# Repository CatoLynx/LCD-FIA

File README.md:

# What's this?
It's my project of converting an old LCD platform passenger information display to be fully customizable!

# BOMs
The BOM for the FIAControl main controller board can be found [here](https://catolynx.github.io/LCD-FIA/Hardware/FIAControl/bom/ibom.html).

The BOM for the FIAPi Raspberry Pi HAT adapter board can be found [here](https://catolynx.github.io/LCD-FIA/Hardware/FIAPi/bom/ibom.html).

# Pictures

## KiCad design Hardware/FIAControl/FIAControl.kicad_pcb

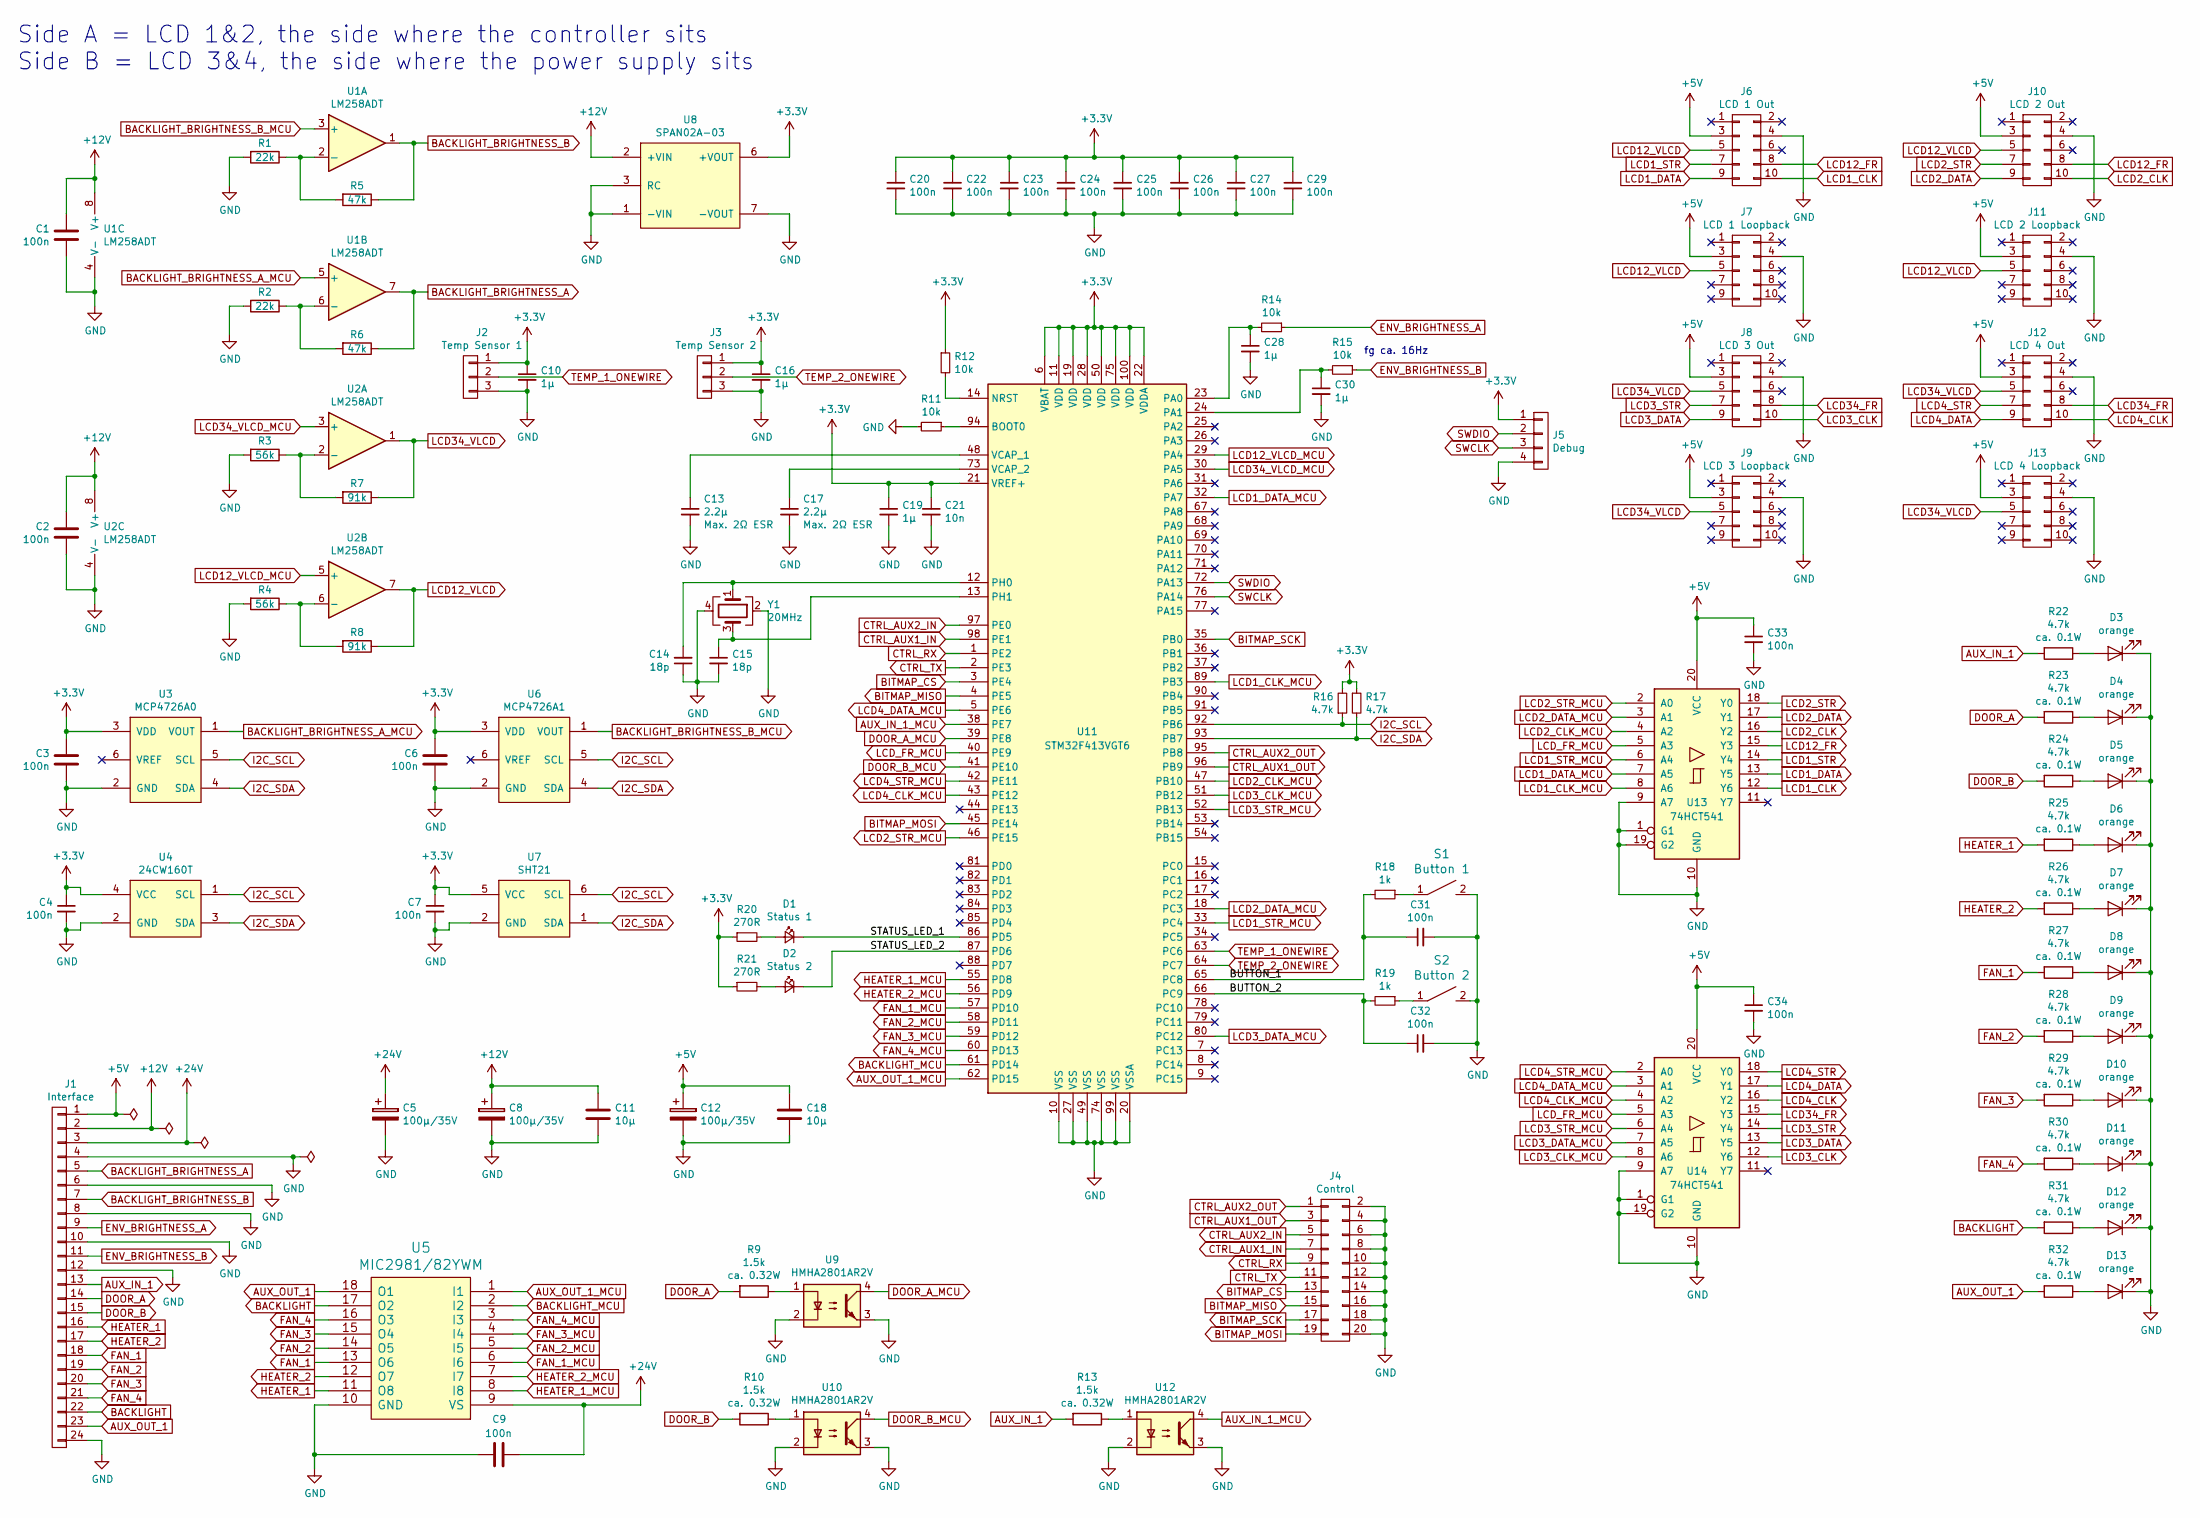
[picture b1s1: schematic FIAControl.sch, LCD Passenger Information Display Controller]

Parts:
C1, C2, C3, C4, C6, C7, C9, C31, C32, C33, C34: 100n; C_0603
C5, C8, C12: 100µ/35V; CP_Elec_6.3x7.7
C10, C16, C28, C30: 1µ; C_0805
C11, C18: 10µ; C_0805
C13, C17: 2.2µ; C_0402
C14, C15: 18p; C_0402
C19: 1µ; C_0402
C20, C22, C23, C24, C25, C26, C27, C29: 100n; C_0402
C21: 10n; C_0402
D1: Status 1; LED_0603
D2: Status 2; LED_0603
D3, D4, D5, D6, D7, D8, D9, D10, D11, D12, D13: orange; LED_0603
J1: Interface; Connector_DEGSON_DG246-3.81_24pin
J2: Temp Sensor 1; Molex_1718560003
J3: Temp Sensor 2; Molex_1718560003
J4: Control; IDC_Header_Straight_20pins
J5: Debug; Pin_Header_Straight_1x04
J6: LCD 1 Out; Connector_IDC_2mm_10pin_THT_Straight
J7: LCD 1 Loopback; Connector_IDC_2mm_10pin_THT_Straight
J8: LCD 3 Out; Connector_IDC_2mm_10pin_THT_Straight
J9: LCD 3 Loopback; Connector_IDC_2mm_10pin_THT_Straight
J10: LCD 2 Out; Connector_IDC_2mm_10pin_THT_Straight
J11: LCD 2 Loopback; Connector_IDC_2mm_10pin_THT_Straight
J12: LCD 4 Out; Connector_IDC_2mm_10pin_THT_Straight
J13: LCD 4 Loopback; Connector_IDC_2mm_10pin_THT_Straight
R1, R2: 22k; R_0603
R3, R4: 56k; R_0603
R5, R6: 47k; R_0603
R7, R8: 91k; R_0603
R9, R10, R13: 1.5k; R_1206
R11, R12, R14, R15: 10k; R_0603
R16, R17: 4.7k; R_0603
R18, R19: 1k; R_0603
R20, R21: 270R; R_0603
R22, R23, R24, R25, R26, R27, R28, R29, R30, R31, R32: 4.7k; R_0805
S1: Button 1; SW_SPST_SKQG
S2: Button 2; SW_SPST_SKQG
U1, U2: LM258ADT; SOIC-8_3.9x4.9mm_Pitch1.27mm
U3: MCP4726A0; SOT-23-6
U4: 24CW160T; SOT-23-5
U5: MIC2981/82YWM; SOIC-18W_7.5x11.6mm_Pitch1.27mm
U6: MCP4726A1; SOT-23-6
U7: SHT21; DFN6_3mmx3mm_EP_P1mm
U8: SPAN02A-03; DC_DC_Converter_MeanWell_SPAN
U9, U10, U12: HMHA2801AR2V; Optocoupler_MiniFlat_HalfPitch_4pin_SMD
U11: STM32F413VGT6; LQFP-100_14x14mm_Pitch0.5mm
U13, U14: 74HCT541; SOIC-20W_7.5x12.8mm_Pitch1.27mm
Y1: 20MHz; Crystal_SMD_2520-4pin_2.5x2.0mm

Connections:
+3V3: C3.2, C4.1, C6.2, C7.1, C10.1, C16.1, C19.1, C20.1, C21.1, C22.1, C23.1, C24.1, C25.1, C26.1, C27.1, C29.1, J2.1, J3.1, J5.1, R12.1, R16.2, R17.1, R20.1, R21.1, U3.3 (VDD), U4.4 (VCC), U6.3 (VDD), U7.5 (VCC), U8.6 (+VOUT), U11.6 (VBAT), U11.11 (VDD), U11.19 (VDD), U11.21 (VREF+), U11.22 (VDDA), U11.28 (VDD), U11.50 (VDD), U11.75 (VDD), U11.100 (VDD)
+5V: C12.1, C18.1, C33.1, C34.1, J1.1, J6.3, J7.3, J8.3, J9.3, J10.3, J11.3, J12.3, J13.3, U13.20 (VCC), U14.20 (VCC)
+12V: C1.2, C2.2, C8.1, C11.1, J1.2, U1.8 (V+), U2.8 (V+), U8.2 (+VIN)
+24V: C5.1, C9.2, J1.3, U5.9 (VS)
/BUTTON_1: C31.1, R18.2, U11.65 (PC8)
/BUTTON_2: C32.1, R19.2, U11.66 (PC9)
/STATUS_LED_1: D1.1 (K), U11.86 (PD5)
/STATUS_LED_2: D2.1 (K), U11.87 (PD6)
AUX_IN_1: J1.13, R13.2, R22.2
AUX_IN_1_MCU: U11.38 (PE7), U12.4
AUX_OUT_1: J1.23, R32.2, U5.18 (O1)
AUX_OUT_1_MCU: U5.1 (I1), U11.62 (PD15)
BACKLIGHT: J1.22, R31.2, U5.17 (O2)
BACKLIGHT_BRIGHTNESS_A: J1.5, R6.1, U1.7
BACKLIGHT_BRIGHTNESS_A_MCU: U1.5 (+), U3.1 (VOUT)
BACKLIGHT_BRIGHTNESS_B: J1.7, R5.1, U1.1
BACKLIGHT_BRIGHTNESS_B_MCU: U1.3 (+), U6.1 (VOUT)
BACKLIGHT_MCU: U5.2 (I2), U11.61 (PD14)
BITMAP_CS: J4.13, U11.3 (PE4)
BITMAP_MISO: J4.15, U11.4 (PE5)
BITMAP_MOSI: J4.19, U11.45 (PE14)
BITMAP_SCK: J4.17, U11.35 (PB0)
CTRL_AUX1_IN: J4.7, U11.98 (PE1)
CTRL_AUX1_OUT: J4.3, U11.96 (PB9)
CTRL_AUX2_IN: J4.5, U11.97 (PE0)
CTRL_AUX2_OUT: J4.1, U11.95 (PB8)
CTRL_RX: J4.9, U11.1 (PE2)
CTRL_TX: J4.11, U11.2 (PE3)
DOOR_A: J1.14, R9.2, R23.2
DOOR_A_MCU: U9.4, U11.39 (PE8)
DOOR_B: J1.15, R10.2, R24.2
DOOR_B_MCU: U10.4, U11.41 (PE10)
ENV_BRIGHTNESS_A: J1.9, R14.1
ENV_BRIGHTNESS_B: J1.11, R15.1
FAN_1: J1.18, R27.2, U5.13 (O6)
FAN_1_MCU: U5.6 (I6), U11.57 (PD10)
FAN_2: J1.19, R28.2, U5.14 (O5)
FAN_2_MCU: U5.5 (I5), U11.58 (PD11)
FAN_3: J1.20, R29.2, U5.15 (O4)
FAN_3_MCU: U5.4 (I4), U11.59 (PD12)
FAN_4: J1.21, R30.2, U5.16 (O3)
FAN_4_MCU: U5.3 (I3), U11.60 (PD13)
GND: C1.1, C2.1, C3.1, C4.2, C5.2, C6.1, C7.2, C8.2, C9.1, C10.2, C11.2, C12.2, C13.2, C14.1, C15.2, C16.2, C17.2, C18.2, C19.2, C20.2, C21.2, C22.2, C23.2, C24.2, C25.2, C26.2, C27.2, C28.2, C29.2, C30.2, C31.2, C32.2, C33.2, C34.2, D3.1 (K), D4.1 (K), D5.1 (K), D6.1 (K), D7.1 (K), D8.1 (K), D9.1 (K), D10.1 (K), D11.1 (K), D12.1 (K), D13.1 (K), J1.4, J1.6, J1.8, J1.10, J1.12, J1.24, J2.3, J3.3, J4.2, J4.4, J4.6, J4.8, J4.10, J4.12, J4.14, J4.16, J4.18, J4.20, J5.4, J6.4, J7.4, J8.4, J9.4, J10.4, J11.4, J12.4, J13.4, R1.2, R2.2, R3.2, R4.2, R11.2, S1.2, S2.2, U1.4 (V-), U2.4 (V-), U3.2 (GND), U4.2 (GND), U5.10 (GND), U6.2 (GND), U7.2 (GND), U8.1 (-VIN), U8.3 (RC), U8.7 (-VOUT), U9.2, U9.3, U10.2, U10.3, U11.10 (VSS), U11.20 (VSSA), U11.27 (VSS), U11.49 (VSS), U11.74 (VSS), U11.99 (VSS), U12.2, U12.3, U13.1 (G1), U13.9 (A7), U13.10 (GND), U13.19 (G2), U14.1 (G1), U14.9 (A7), U14.10 (GND), U14.19 (G2), Y1.2, Y1.4
HEATER_1: J1.16, R25.2, U5.11 (O8)
HEATER_1_MCU: U5.8 (I8), U11.55 (PD8)
HEATER_2: J1.17, R26.2, U5.12 (O7)
HEATER_2_MCU: U5.7 (I7), U11.56 (PD9)
I2C_SCL: R16.1, U3.5 (SCL), U4.1 (SCL), U6.5 (SCL), U7.6 (SCL), U11.92 (PB6)
I2C_SDA: R17.2, U3.4 (SDA), U4.3 (SDA), U6.4 (SDA), U7.1 (SDA), U11.93 (PB7)
LCD1_CLK: J6.10, U13.12 (Y6)
LCD1_CLK_MCU: U11.89 (PB3), U13.8 (A6)
LCD1_DATA: J6.9, U13.13 (Y5)
LCD1_DATA_MCU: U11.32 (PA7), U13.7 (A5)
LCD1_STR: J6.7, U13.14 (Y4)
LCD1_STR_MCU: U11.33 (PC4), U13.6 (A4)
LCD2_CLK: J10.10, U13.16 (Y2)
LCD2_CLK_MCU: U11.47 (PB10), U13.4 (A2)
LCD2_DATA: J10.9, U13.17 (Y1)
LCD2_DATA_MCU: U11.18 (PC3), U13.3 (A1)
LCD2_STR: J10.7, U13.18 (Y0)
LCD2_STR_MCU: U11.46 (PE15), U13.2 (A0)
LCD3_CLK: J8.10, U14.12 (Y6)
LCD3_CLK_MCU: U11.51 (PB12), U14.8 (A6)
LCD3_DATA: J8.9, U14.13 (Y5)
LCD3_DATA_MCU: U11.80 (PC12), U14.7 (A5)
LCD3_STR: J8.7, U14.14 (Y4)
LCD3_STR_MCU: U11.52 (PB13), U14.6 (A4)
LCD4_CLK: J12.10, U14.16 (Y2)
LCD4_CLK_MCU: U11.43 (PE12), U14.4 (A2)
LCD4_DATA: J12.9, U14.17 (Y1)
LCD4_DATA_MCU: U11.5 (PE6), U14.3 (A1)
LCD4_STR: J12.7, U14.18 (Y0)
LCD4_STR_MCU: U11.42 (PE11), U14.2 (A0)
LCD12_FR: J6.8, J10.8, U13.15 (Y3)
LCD12_VLCD: J6.5, J7.5, J10.5, J11.5, R8.1, U2.7
LCD12_VLCD_MCU: U2.5 (+), U11.29 (PA4)
LCD34_FR: J8.8, J12.8, U14.15 (Y3)
LCD34_VLCD: J8.5, J9.5, J12.5, J13.5, R7.1, U2.1
LCD34_VLCD_MCU: U2.3 (+), U11.30 (PA5)
LCD_FR_MCU: U11.40 (PE9), U13.5 (A3), U14.5 (A3)
unnamed: C13.1, U11.48 (VCAP_1)
unnamed: C14.2, U11.12 (PH0), Y1.1
unnamed: C15.1, U11.13 (PH1), Y1.3
unnamed: C17.1, U11.73 (VCAP_2)
unnamed: C28.1, R14.2, U11.23 (PA0)
unnamed: C30.1, R15.2, U11.24 (PA1)
unnamed: D1.2 (A), R20.2
unnamed: D2.2 (A), R21.2
unnamed: D3.2 (A), R22.1
unnamed: D4.2 (A), R23.1
unnamed: D5.2 (A), R24.1
unnamed: D6.2 (A), R25.1
unnamed: D7.2 (A), R26.1
unnamed: D8.2 (A), R27.1
unnamed: D9.2 (A), R28.1
unnamed: D10.2 (A), R29.1
unnamed: D11.2 (A), R30.1
unnamed: D12.2 (A), R31.1
unnamed: D13.2 (A), R32.1
unnamed: R1.1, R5.2, U1.2 (-)
unnamed: R2.1, R6.2, U1.6 (-)
unnamed: R3.1, R7.2, U2.2 (-)
unnamed: R4.1, R8.2, U2.6 (-)
unnamed: R9.1, U9.1
unnamed: R10.1, U10.1
unnamed: R11.1, U11.94 (BOOT0)
unnamed: R12.2, U11.14 (NRST)
unnamed: R13.1, U12.1
unnamed: R18.1, S1.1
unnamed: R19.1, S2.1
SWCLK: J5.3, U11.76 (PA14)
SWDIO: J5.2, U11.72 (PA13)
TEMP_1_ONEWIRE: J2.2, U11.63 (PC6)
TEMP_2_ONEWIRE: J3.2, U11.64 (PC7)

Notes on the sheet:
Side A = LCD 1&2, the side where the controller sits Side B = LCD 3&4, the side where the power supply sits
fg ca. 16Hz

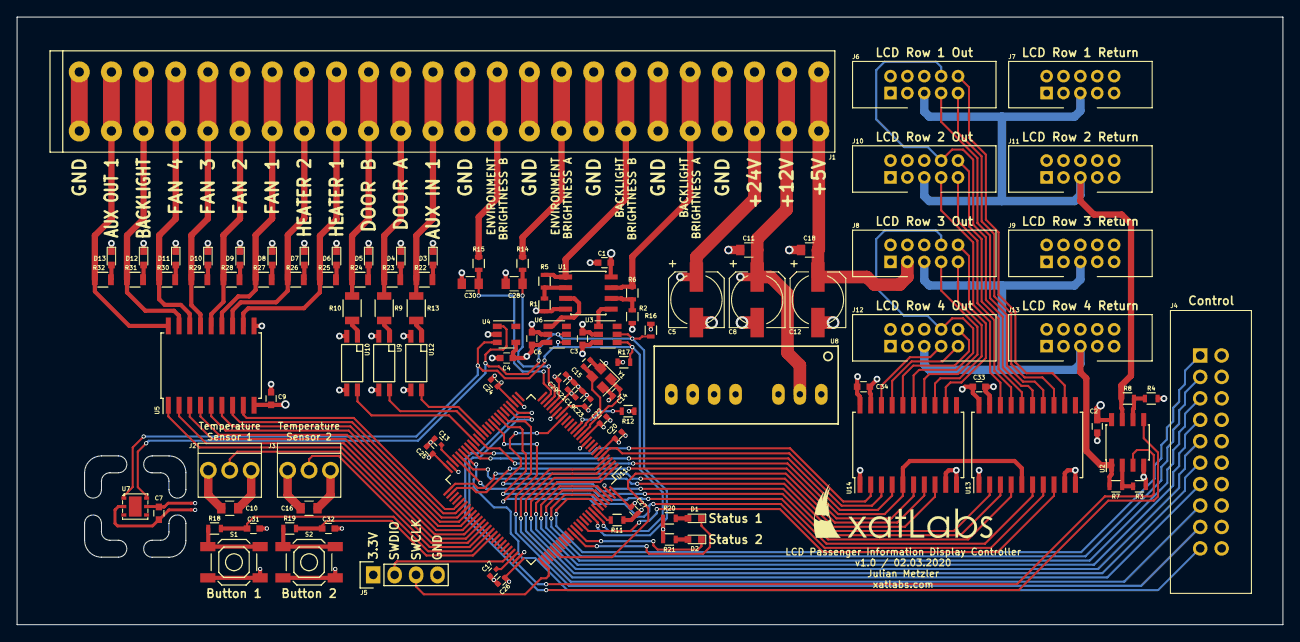
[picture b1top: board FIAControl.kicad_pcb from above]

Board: 4 copper layers, 150.0 x 72.0 mm, 109 parts (0 on the bottom side), 114 nets.

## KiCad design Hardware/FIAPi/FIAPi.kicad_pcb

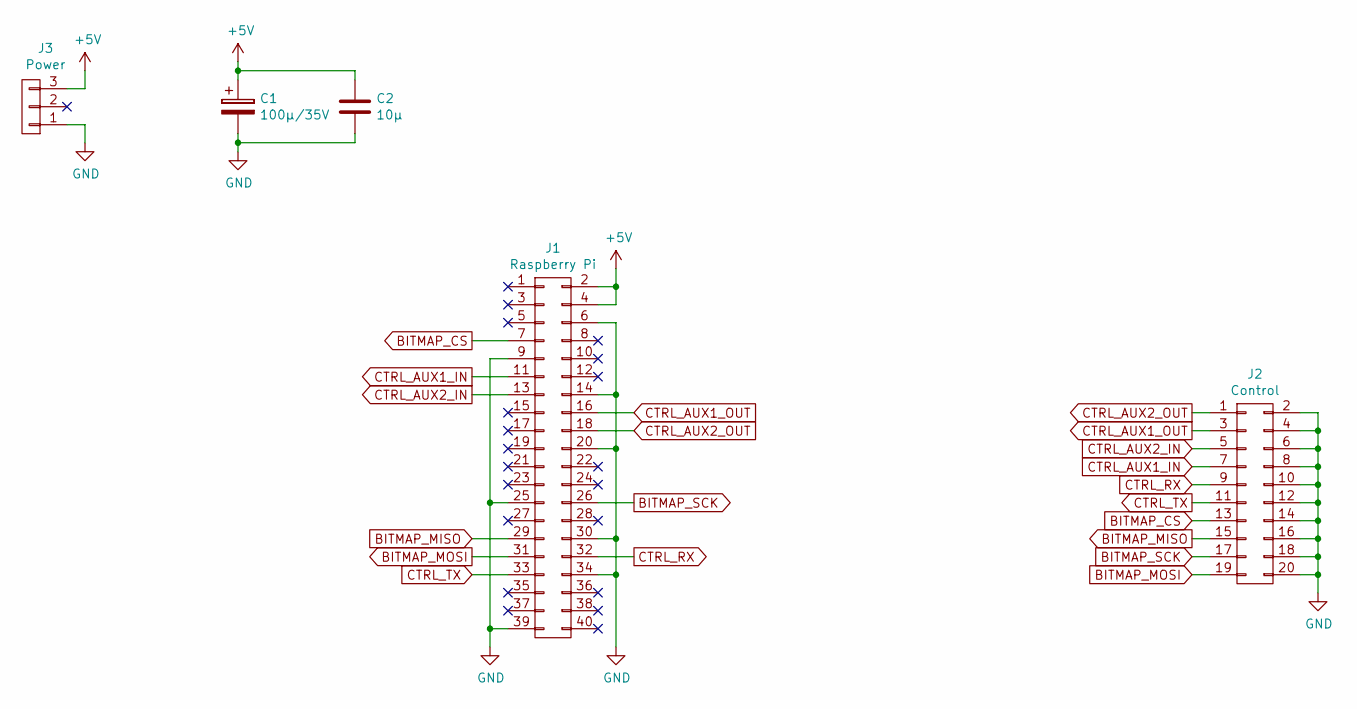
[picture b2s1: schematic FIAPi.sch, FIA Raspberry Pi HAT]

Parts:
C1: 100µ/35V; CP_Elec_6.3x7.7
C2: 10µ; C_0805
J1: Raspberry Pi; Socket_Strip_Straight_2x20
J2: Control; IDC_Header_Straight_20pins
J3: Power; Connector_DEGSON_DG246-3.81_3pin

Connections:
+5V: C1.1, C2.1, J1.2, J1.4, J3.3
BITMAP_CS: J1.7, J2.13
BITMAP_MISO: J1.29, J2.15
BITMAP_MOSI: J1.31, J2.19
BITMAP_SCK: J1.26, J2.17
CTRL_AUX1_IN: J1.11, J2.7
CTRL_AUX1_OUT: J1.16, J2.3
CTRL_AUX2_IN: J1.13, J2.5
CTRL_AUX2_OUT: J1.18, J2.1
CTRL_RX: J1.32, J2.9
CTRL_TX: J1.33, J2.11
GND: C1.2, C2.2, J1.6, J1.9, J1.14, J1.20, J1.25, J1.30, J1.34, J1.39, J2.2, J2.4, J2.6, J2.8, J2.10, J2.12, J2.14, J2.16, J2.18, J2.20, J3.1

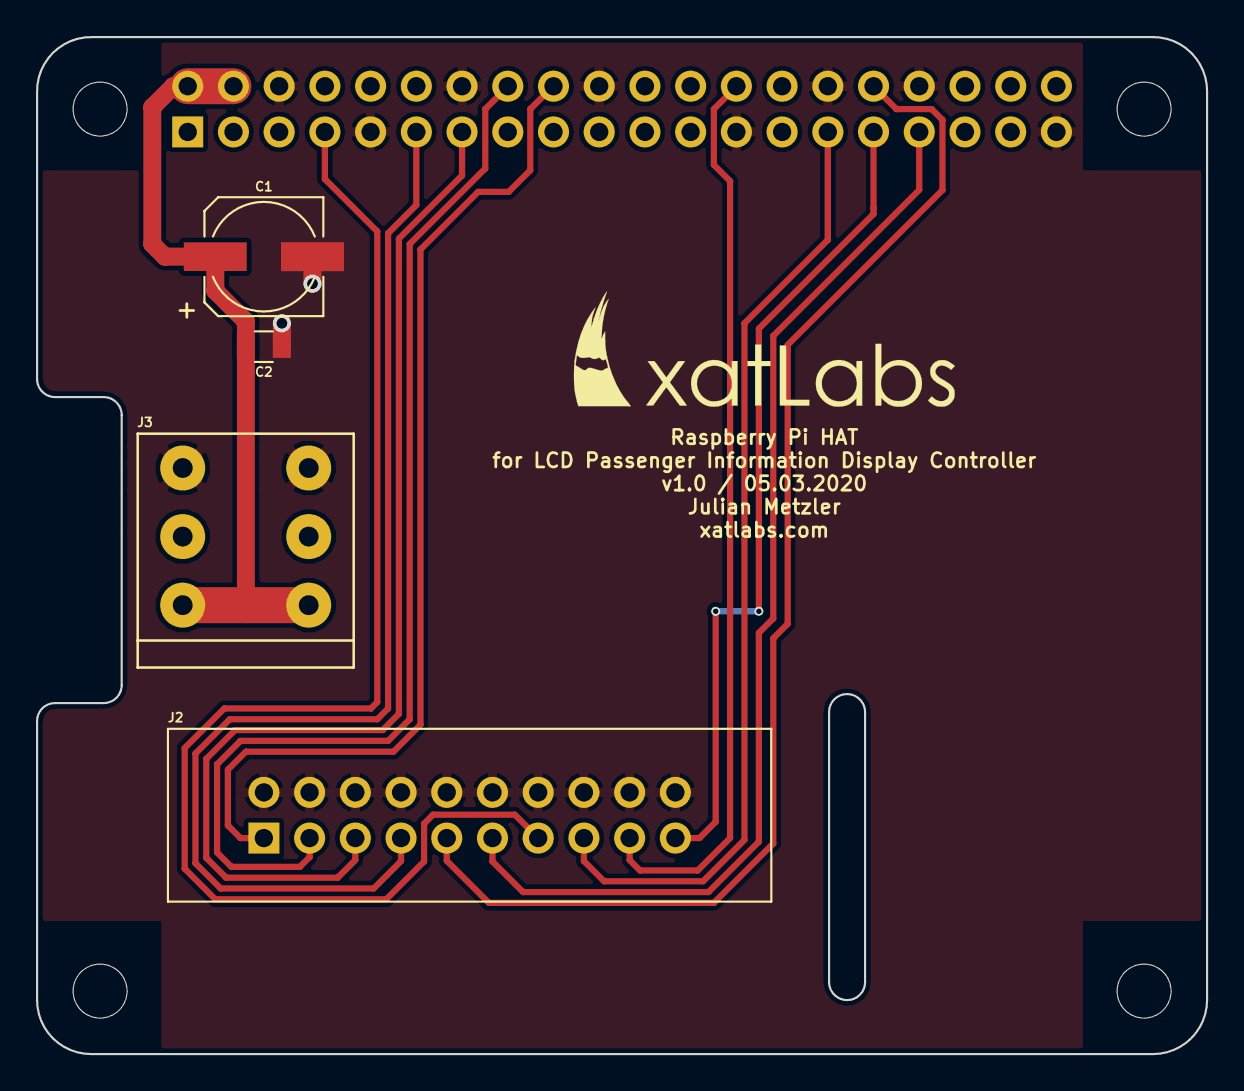
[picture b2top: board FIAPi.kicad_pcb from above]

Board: 2 copper layers, 65.0 x 56.5 mm, 5 parts (1 on the bottom side), 12 nets.

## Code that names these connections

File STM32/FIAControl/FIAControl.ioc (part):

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PB13.GPIOParameters=GPIO_Label
PD12.GPIO_Label=FAN_3
PC7.GPIOParameters=GPIO_PuPd,GPIO_Label
PE11.GPIOParameters=GPIO_Label
PB10.Mode=TX_Only_Simplex_Unidirect_Master
PC12.Signal=SPI3_MOSI
PE8.GPIO_PuPd=GPIO_PULLUP
PC6.GPIO_Label=TEMP_1_ONEWIRE
PE10.GPIO_PuPd=GPIO_PULLUP
PB13.Signal=GPIO_Output
PD6.GPIO_Label=STATUS_LED_2
PE6.GPIO_Label=LCD4_MOSI
RCC.SYSCLKSource=RCC_SYSCLKSOURCE_PLLCLK
PD15.GPIOParameters=GPIO_Label
PE2.Mode=Asynchronous
PB6.Signal=I2C1_SCL
PC7.Signal=GPIO_Input
PB6.Mode=I2C
PC3.Signal=SPI2_MOSI
PD8.Signal=GPIO_Output
PE5.Signal=SPI5_MISO
PE1.Signal=GPIO_Input
PB3.Mode=TX_Only_Simplex_Unidirect_Master
PB12.GPIO_Label=LCD3_SCK
PB0.GPIOParameters=GPIO_Label
PE0.GPIOParameters=GPIO_Label
PA1.GPIOParameters=GPIO_Label
PC4.GPIO_Label=LCD1_LATCH
PE9.Signal=S_TIM1_CH1
PE4.GPIO_Label=BITMAP_CS
PE2.Signal=UART10_RX
PE10.Signal=GPIO_Input
PA0.Signal=ADCx_IN0
PC8.GPIOParameters=GPIO_PuPd,GPIO_Label
Mcu.Package=LQFP100
PB9.Signal=GPIO_Output
PE10.GPIOParameters=GPIO_PuPd,GPIO_Label
PD12.Signal=GPIO_Output
PD5.GPIOParameters=GPIO_Label,GPIO_ModeDefaultOutputPP
PE12.GPIO_Label=LCD4_SCK
PC6.GPIO_PuPd=GPIO_PULLUP
PA5.GPIOParameters=GPIO_Label
PB10.GPIOParameters=GPIO_Label
PE10.GPIO_Label=DOOR_B
PD6.GPIO_ModeDefaultOutputPP=GPIO_MODE_OUTPUT_OD
PA4.GPIO_Label=CONTRAST_1
PD15.Signal=GPIO_Output
PC4.GPIOParameters=GPIO_Label
PE12.Mode=TX_Only_Simplex_Unidirect_Master
PD6.GPIOParameters=GPIO_Label,GPIO_ModeDefaultOutputPP
PD9.GPIO_Label=HEATER_2
PH1\ -\ OSC_OUT.Mode=HSE-External-Oscillator
PC6.Signal=GPIO_Input
PD13.GPIOParameters=GPIO_Label
PC3.GPIOParameters=GPIO_Label
PD10.Signal=GPIO_Output
PB8.GPIO_Label=CTRL_AUX2_OUT
PE8.GPIO_Label=DOOR_A
PC7.GPIO_PuPd=GPIO_PULLUP
PE9.GPIO_Label=LCD_FRAME
PB10.Signal=SPI2_SCK
PA5.Signal=COMP_DAC2_group
PC12.Mode=TX_Only_Simplex_Unidirect_Master
PH1\ -\ OSC_OUT.Signal=RCC_OSC_OUT
PE1.GPIO_Label=CTRL_AUX1_IN
PE14.Signal=SPI5_MOSI
PE6.Mode=TX_Only_Simplex_Unidirect_Master
PE15.Signal=GPIO_Output
PE8.Signal=GPIO_Input
PA1.GPIO_Label=BRIGHTNESS_IN_2
PC9.GPIO_PuPd=GPIO_PULLUP
PA13.Mode=Serial_Wire
PC9.GPIOParameters=GPIO_PuPd,GPIO_Label
PC7.GPIO_Label=TEMP_2_ONEWIRE
PC8.GPIO_PuPd=GPIO_PULLUP
PA4.Signal=COMP_DAC1_group
PD14.GPIOParameters=GPIO_Label
PA5.GPIO_Label=CONTRAST_2
PD11.Signal=GPIO_Output
PE5.GPIO_Label=BITMAP_MISO
PC12.GPIO_Label=LCD3_MOSI
PA0.GPIOParameters=GPIO_Label
PE3.Signal=UART10_TX
PC3.GPIO_Label=LCD2_MOSI
PD5.GPIO_ModeDefaultOutputPP=GPIO_MODE_OUTPUT_OD
PE12.GPIOParameters=GPIO_Label
PB0.Signal=SPI5_SCK
PA7.GPIOParameters=GPIO_Label
PB12.GPIOParameters=GPIO_Label
PC3.Mode=TX_Only_Simplex_Unidirect_Master
PE7.GPIO_PuPd=GPIO_PULLUP
Mcu.UserName=STM32F413VGTx
PD9.GPIOParameters=GPIO_Label
PE11.GPIO_Label=LCD4_LATCH
PA0.GPIO_Label=BRIGHTNESS_IN_1
PB0.GPIO_Label=BITMAP_SCK
PB13.GPIO_Label=LCD3_LATCH
PE5.GPIOParameters=GPIO_Label
PD13.Signal=GPIO_Output
PE4.GPIOParameters=GPIO_Label,GPIO_ModeDefaultEXTI
PH0\ -\ OSC_IN.Signal=RCC_OSC_IN
PD11.GPIO_Label=FAN_2
PD8.GPIOParameters=PinState,GPIO_Label
PD10.GPIOParameters=GPIO_Label
RCC.HSE_VALUE=20000000
PA14.Mode=Serial_Wire
PE3.GPIOParameters=GPIO_Label
PB3.GPIOParameters=GPIO_Label
PB7.Signal=I2C1_SDA
PE4.Signal=GPXTI4
PE6.GPIOParameters=GPIO_Label
PD13.GPIO_Label=FAN_4
PB12.Mode=TX_Only_Simplex_Unidirect_Master
PD5.GPIO_Label=STATUS_LED_1
PE0.GPIO_Label=CTRL_AUX2_IN
PE7.Signal=GPXTI7
PD6.Signal=GPIO_Output
PE2.GPIO_Label=CTRL_RX
PE3.Mode=Asynchronous
PB3.GPIO_Label=LCD1_SCK
PE8.GPIOParameters=GPIO_PuPd,GPIO_Label
PB8.GPIOParameters=GPIO_Label
PD15.GPIO_Label=AUX_OUT_1
PA7.Mode=TX_Only_Simplex_Unidirect_Master
PE14.GPIOParameters=GPIO_Label
PB9.GPIO_Label=CTRL_AUX1_OUT
PC9.GPIO_Label=BUTTON_2
PC8.Signal=GPIO_Input
PC4.Signal=GPIO_Output
PE4.GPIO_ModeDefaultEXTI=GPIO_MODE_IT_RISING_FALLING
PE14.GPIO_Label=BITMAP_MOSI
PD9.Signal=GPIO_Output
PD5.Signal=GPIO_Output
PE9.GPIOParameters=GPIO_Label
PE15.GPIOParameters=GPIO_Label
PD8.GPIO_Label=HEATER_1
PB9.GPIOParameters=GPIO_Label
PC8.GPIO_Label=BUTTON_1
PC12.GPIOParameters=GPIO_Label
PA13.Signal=SYS_JTMS-SWDIO
PH0\ -\ OSC_IN.Mode=HSE-External-Oscillator
PE15.GPIO_Label=LCD2_LATCH
PD12.GPIOParameters=GPIO_Label
PB10.GPIO_Label=LCD2_SCK
PE7.GPIOParameters=GPIO_PuPd,GPIO_Label,GPIO_ModeDefaultEXTI
PE2.GPIOParameters=GPIO_Label
PD10.GPIO_Label=FAN_1
PE11.Signal=GPIO_Output
PA1.Signal=ADCx_IN1
PB0.Mode=Full_Duplex_Slave
board=custom
PD11.GPIOParameters=GPIO_Label
PE14.Mode=Full_Duplex_Slave
PE5.Mode=Full_Duplex_Slave
PE7.GPIO_ModeDefaultEXTI=GPIO_MODE_IT_RISING_FALLING
PD14.GPIO_Label=LIGHT
PA4.GPIOParameters=GPIO_Label
PE6.Signal=SPI4_MOSI
Mcu.Name=STM32F413V(G-H)Tx
PE0.Signal=GPIO_Input
PE7.GPIO_Label=AUX_IN_1
PE12.Signal=SPI4_SCK
PD14.Signal=GPIO_Output
PB3.Signal=SPI1_SCK
RCC.SYSCLKFreq_VALUE=100000000
PA7.GPIO_Label=LCD1_MOSI
PB7.Mode=I2C
PA14.Signal=SYS_JTCK-SWCLK
PC6.GPIOParameters=GPIO_PuPd,GPIO_Label
PB8.Signal=GPIO_Output
PE3.GPIO_Label=CTRL_TX
PC9.Signal=GPIO_Input
PD8.PinState=GPIO_PIN_RESET
PB12.Signal=SPI3_SCK
PE1.GPIOParameters=GPIO_Label
PA7.Signal=SPI1_MOSI

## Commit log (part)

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2020-02-18 Improvements to layout renderer (new layouts and options)
2020-03-02 First revision of STM32 controller board
2020-03-02 Prepared CubeMX project for STM32 controller board
2020-03-02 Added Gerber dirs to .gitignore
2020-03-05 Fixed incorrect label directions on Control header in FIAControl schematic
2020-03-21 Added Raspberry Pi high-level stuff
2020-03-21 Added first barely functional version of FIAControl STM32 firmware
2020-03-21 Removed gcode files
2020-03-21 Renamed Raspberry Pi folder
2020-03-21 Added virtualenv to gitignore
2020-03-21 STM32: added more comments and improved structure
2020-03-21 STM32: Reworked side-dependent code and added brightness 0 on door open
2020-03-21 Hardware: Added To-Do list
2020-03-22 STM32: Added UART protocol
2020-03-22 Hardware: Updated TODO
2020-03-22 RasPi: Added first draft of FIA lib and test script
2020-03-22 RasPi: Added temperature logger and status monitor, renamed layouts
2020-03-22 STM32: Improved handling of backlight brightness, added cmds to get cur. & env. brightness
2020-03-24 STM32: Added MCU Reset UART command
2020-03-24 RasPi: Added MCU Reset UART command and fixed DB live departure script
2020-04-02 RasPi: Added OpenOCD server configuration for remote debugging / flashing
2020-04-02 STM32: Updated PIO config for remote debugging / flashing
2020-04-02 RasPi: Added back ST-LINK USB IDs and removed unnecessary WORKAREA definition from OpenOCD config
2020-04-06 STM32: Tweaked LCD FR timer values for more accurate duty cycle
2020-04-06 RasPi: Added LCD contrast UART commands
2020-04-06 Hardware: Updated todo, added LTSpice sim of LCD contrast power stage
2020-04-07 STM32: Only update brightness DACs when door status or ADC average changed
2020-04-09 RasPi: Updated live departures to use pyDBInfoscreen lib, added delay rounding
2020-04-12 STM32: Changed startup sequence to be less harsh on the power supply
2020-04-13 STM32: Rewrote bitmap rendering to work with regular col-major bitmaps
2020-04-13 RasPi: Updated FIA class to work with 93716b3
2020-04-13 STM32: Moved main code to fia.c, prepared SPI Rx CS functionality
2020-04-14 STM32: Implemented proper SPI Rx CS handling (Bitmap Rx)
2020-04-14 RasPi: Updated UART commands acc. to 605bb0a and removed MCU reset from DB dep. screen
2020-04-18 STM32: Added correct linker file path
2020-04-18 STM32: Added temp. regulation and prepared support for scroll buffers, minor restructuring
2020-04-19 STM32: Separated LCD update code, prepared mask buffer support, changed temp. reg. thresholds
2020-04-19 STM32: Updated malloc to allow reallocating blocks of exact same size
2020-04-19 STM32: Updated temperature regulation values
2020-04-25 STM32: Fixed incorrect LCD data on different panel counts, made FR freq configurable
2020-04-25 STM32: Added auto-format config file
2020-05-02 RasPi: Updated DB departure layout with new fonts
2020-05-02 Added image and readme
2020-05-05 RasPi: Added coach order to DB live departures
2020-05-05 RasPi: Added interactive script and updated .gitignore
2020-05-07 RasPi: Added CCC talk schedule layout, improved LayoutRenderer CLI
2020-05-07 RasPi: Improved image display script, added ffmpeg notes
2020-05-07 RasPi: Added frame dropping to display_image.py
2020-05-10 STM32: Fixed temperature regulation criteria
2020-05-10 STM32: Changed default contrast
2020-05-14 Added temperature measurement spreadsheet
2020-05-14 STM32: Disable fans when door is open
2020-05-17 RasPi: Add support for platform selection to DB live departures
2020-06-01 RasPi: Update DB scripts to use new lib, add platform list script
2020-06-07 RasPi: Add Conway's Game of Life
2020-07-03 RasPi: Fix render_image missing parameter
2020-07-04 Tools: Fully working scroll buffer test script
2020-07-04 Tools: Optimizations to scroll buffer test script
2020-07-04 STM32: Add -O3 build flag
2020-07-04 STM32: Scroll buffer rendering, mask buffers as bitmap targets
2020-07-05 RasPi: Update lib with new STM32 changes, improve interactive.py
2020-07-08 STM32: Make mask optional, reorder cmds, add GET_DESTINATION_BUFFER cmd
2020-07-08 RasPi: Stop writing debug json file
2020-07-08 RasPi: Add new commands
2020-07-19 STM32: Decrease BL ballast temp (after 2 broken ballasts)
2020-07-20 Add interactive BOMs
2020-07-20 Dark mode in BOMs, name change
2020-07-20 Fix link in readme
2020-07-26 RasPi: Add QOS messages to train info message
2020-07-26 RasPi: Add local config file
2020-07-26 RasPi: Add timed backlight by AUX1 input
2020-07-26 RasPi: Add train type filter to live departures
2020-07-26 RasPi: Update requirements.txt
2020-07-27 RasPi: Add destination replacmeent
2020-07-29 RasPi: Add more replacements
2020-07-31 RasPi: Restructure replacement system to use individual json files
2020-08-13 RasPi: Add FIA emulator class (shows contents in a Tk window)
2020-08-13 RasPi: Add frame colour to emulator
2020-08-13 RasPi: Add numpy dependency
2020-08-13 RasPi: Tweak emulator colours and sizes
2020-08-14 RasPi: Modify display_image to expose the render function
2020-08-14 RasPi: First version of event display tool
2020-08-15 RasPi: Add fonts as submodule
2020-08-25 RasPi: Add more cmdline arguments to layout renderer
2020-08-25 RasPi: Fix encoding in layouts for event display
2020-08-25 RasPi: Add event display test config and WIP of tweet layout
2020-08-25 RasPi: Change fonts submodule remote
2020-08-25 RasPi: Add multiline text & wrapping to layout renderer, put some code in separate funcs
2020-08-26 RasPi: Move separator line in tweet layout
2020-08-26 RasPi: Add webserver for managing texts for the event display
2020-08-27 RasPi: Fix rendering lines and rects when render_boxes is on
2020-08-27 RasPi: Webserver: Fix font choices
2020-08-27 RasPi: Fix telegram sorting order in event display
2020-08-27 RasPi: Change default line spacing in event display / webserver
2020-08-27 RasPi: Add clearall command to telegram bot
2020-08-28 RasPi: Remove filter in telegram bot
2020-08-28 RasPi: Add error handling in event script
2020-08-28 RasPi: Add /delete command to telegram bot
2020-08-28 RasPi: Remove umlaut replacement in web interface
2020-08-28 Add mastodon support
2020-08-28 RasPi: Add weather to event script
2020-08-28 RasPi: Add socket default timeout to event script
2020-08-28 Fix additional deletions, reorder things
2020-08-28 RasPi: Add environment logging script
2020-08-29 RasPi: Add door states and LCD contrast to env log
2020-08-29 RasPi: Increase weather display duration for vvoidcamp20
2020-08-29 RasPi: Add timeouts to potentially hanging funcs in event script
2020-08-30 RasPi: Add demo animation to vvoidcamp config
2020-09-21 RasPi: Auto-clear scroll buffers after DB departures in event script
2020-10-18 RasPi: Add custom route replacements
2020-10-18 STM32: Increase humidity thresholds
2020-10-19 RasPi: Add replacement in munich.json
2020-10-19 Change LayoutRenderer render behaviour
2020-10-25 RasPi: Add old 5x2 single layout, update .gitignore
2020-10-26 RasPi: Unique trains in DB live departures
2020-11-15 RasPi: Add flag for DBI host to db_live_departures, remove test file
2020-11-15 RasPi: Fix exception when rendering layout to file with layout_renderer
2020-11-15 RasPi: Add script to generate C arrays for images
2020-11-15 STM32: Add splash screens, use build configs instead of config.h
2021-03-20 Bump jinja2 from 2.11.2 to 2.11.3 in /RasPi
    Bumps [jinja2](https://github.com/pallets/jinja) from 2.11.2 to 2.11.3.
    - [Release notes](https://github.com/pallets/jinja/releases)
    - [Changelog](https://github.com/pallets/jinja/blob/master/CHANGES.rst)
    - [Commits](https://github.com/pallets/jinja/compare/2.11.2...2.11.3)
2021-06-02 Bump urllib3 from 1.25.8 to 1.26.5 in /RasPi
    Bumps [urllib3](https://github.com/urllib3/urllib3) from 1.25.8 to 1.26.5.
    - [Release notes](https://github.com/urllib3/urllib3/releases)
    - [Changelog](https://github.com/urllib3/urllib3/blob/main/CHANGES.rst)
    - [Commits](https://github.com/urllib3/urllib3/compare/1.25.8...1.26.5)
    ---
    updated-dependencies:
2021-06-08 Bump pillow from 7.2.0 to 8.2.0 in /RasPi
    Bumps [pillow](https://github.com/python-pillow/Pillow) from 7.2.0 to 8.2.0.
    - [Release notes](https://github.com/python-pillow/Pillow/releases)
    - [Changelog](https://github.com/python-pillow/Pillow/blob/master/CHANGES.rst)
    - [Commits](https://github.com/python-pillow/Pillow/compare/7.2.0...8.2.0)
    ---
    updated-dependencies:
2021-09-08 Bump pillow from 7.2.0 to 8.3.2 in /RasPi
    Bumps [pillow](https://github.com/python-pillow/Pillow) from 7.2.0 to 8.3.2.
    - [Release notes](https://github.com/python-pillow/Pillow/releases)
    - [Changelog](https://github.com/python-pillow/Pillow/blob/master/CHANGES.rst)
    - [Commits](https://github.com/python-pillow/Pillow/compare/7.2.0...8.3.2)
    ---
    updated-dependencies:
2021-12-13 Bump lxml from 4.6.4 to 4.6.5 in /RasPi
    Bumps [lxml](https://github.com/lxml/lxml) from 4.6.4 to 4.6.5.
    - [Release notes](https://github.com/lxml/lxml/releases)
    - [Changelog](https://github.com/lxml/lxml/blob/master/CHANGES.txt)
    - [Commits](https://github.com/lxml/lxml/compare/lxml-4.6.4...lxml-4.6.5)
    ---
    updated-dependencies:
2021-12-18 RasPi: Add departure list layout to DB live departures
2021-12-31 RasPi: Add MQTT backlight control
2022-01-02 RasPi: Improve error handling in mqtt_light
2022-01-13 Bump pillow from 8.4.0 to 9.0.0 in /RasPi
    Bumps [pillow](https://github.com/python-pillow/Pillow) from 8.4.0 to 9.0.0.
    - [Release notes](https://github.com/python-pillow/Pillow/releases)
    - [Changelog](https://github.com/python-pillow/Pillow/blob/main/CHANGES.rst)
    - [Commits](https://github.com/python-pillow/Pillow/compare/8.4.0...9.0.0)
    ---
    updated-dependencies:
2022-01-31 Add client ID and log to mqtt_light
2022-03-12 Bump pillow from 8.4.0 to 9.0.1 in /RasPi
    Bumps [pillow](https://github.com/python-pillow/Pillow) from 8.4.0 to 9.0.1.
    - [Release notes](https://github.com/python-pillow/Pillow/releases)
    - [Changelog](https://github.com/python-pillow/Pillow/blob/main/CHANGES.rst)
    - [Commits](https://github.com/python-pillow/Pillow/compare/8.4.0...9.0.1)
    ---
    updated-dependencies:
2022-06-22 Bump numpy from 1.19.1 to 1.22.0 in /RasPi
    Bumps [numpy](https://github.com/numpy/numpy) from 1.19.1 to 1.22.0.
    - [Release notes](https://github.com/numpy/numpy/releases)
    - [Changelog](https://github.com/numpy/numpy/blob/main/doc/HOWTO_RELEASE.rst)
    - [Commits](https://github.com/numpy/numpy/compare/v1.19.1...v1.22.0)
    ---
    updated-dependencies:
2022-11-22 Bump pillow from 8.4.0 to 9.3.0 in /RasPi
    Bumps [pillow](https://github.com/python-pillow/Pillow) from 8.4.0 to 9.3.0.
    - [Release notes](https://github.com/python-pillow/Pillow/releases)
    - [Changelog](https://github.com/python-pillow/Pillow/blob/main/CHANGES.rst)
    - [Commits](https://github.com/python-pillow/Pillow/compare/8.4.0...9.3.0)
    ---
    updated-dependencies:
2022-12-08 Bump certifi from 2020.6.20 to 2022.12.7 in /RasPi
    Bumps [certifi](https://github.com/certifi/python-certifi) from 2020.6.20 to 2022.12.7.
    - [Release notes](https://github.com/certifi/python-certifi/releases)
    - [Commits](https://github.com/certifi/python-certifi/compare/2020.06.20...2022.12.07)
    ---
    updated-dependencies:
    - dependency-name: certifi
2023-02-16 Bump werkzeug from 1.0.1 to 2.2.3 in /RasPi
    Bumps [werkzeug](https://github.com/pallets/werkzeug) from 1.0.1 to 2.2.3.
    - [Release notes](https://github.com/pallets/werkzeug/releases)
    - [Changelog](https://github.com/pallets/werkzeug/blob/main/CHANGES.rst)
    - [Commits](https://github.com/pallets/werkzeug/compare/1.0.1...2.2.3)
    ---
    updated-dependencies:
2024-03-26 Move variable declarations to C files and init them
2024-03-26 Make UART_MAX_PAYLOAD_LENGTH as small as needed instead of 255
2024-03-26 Only decrement FIA_scrollBufferCount when > 0
2024-03-27 Rename custom malloc/free implementations to avoid confusion with builtins
2024-03-27 Use defines instead of build config for selecting splash screen
2024-03-27 Update init state of FIA_bitmapRxBufID to match other variables
2024-03-27 Bugfix: UART ring buffer peek index didn't wrap around
2024-03-27 Enable watchdog timer
2024-04-02 fia_control: Add num_loops to send_gif
2024-04-02 Add dm_moba script
2024-04-02 STM32: Add product_line field to board definition
2024-04-02 STM32: Pin platform version, fix wrong define
